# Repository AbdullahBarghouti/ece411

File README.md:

# ECE411

Practicum project for ECE 411

# Credits

Travis Hermant

Josh Davis

Abdullah Barghouti

Ammar Khan

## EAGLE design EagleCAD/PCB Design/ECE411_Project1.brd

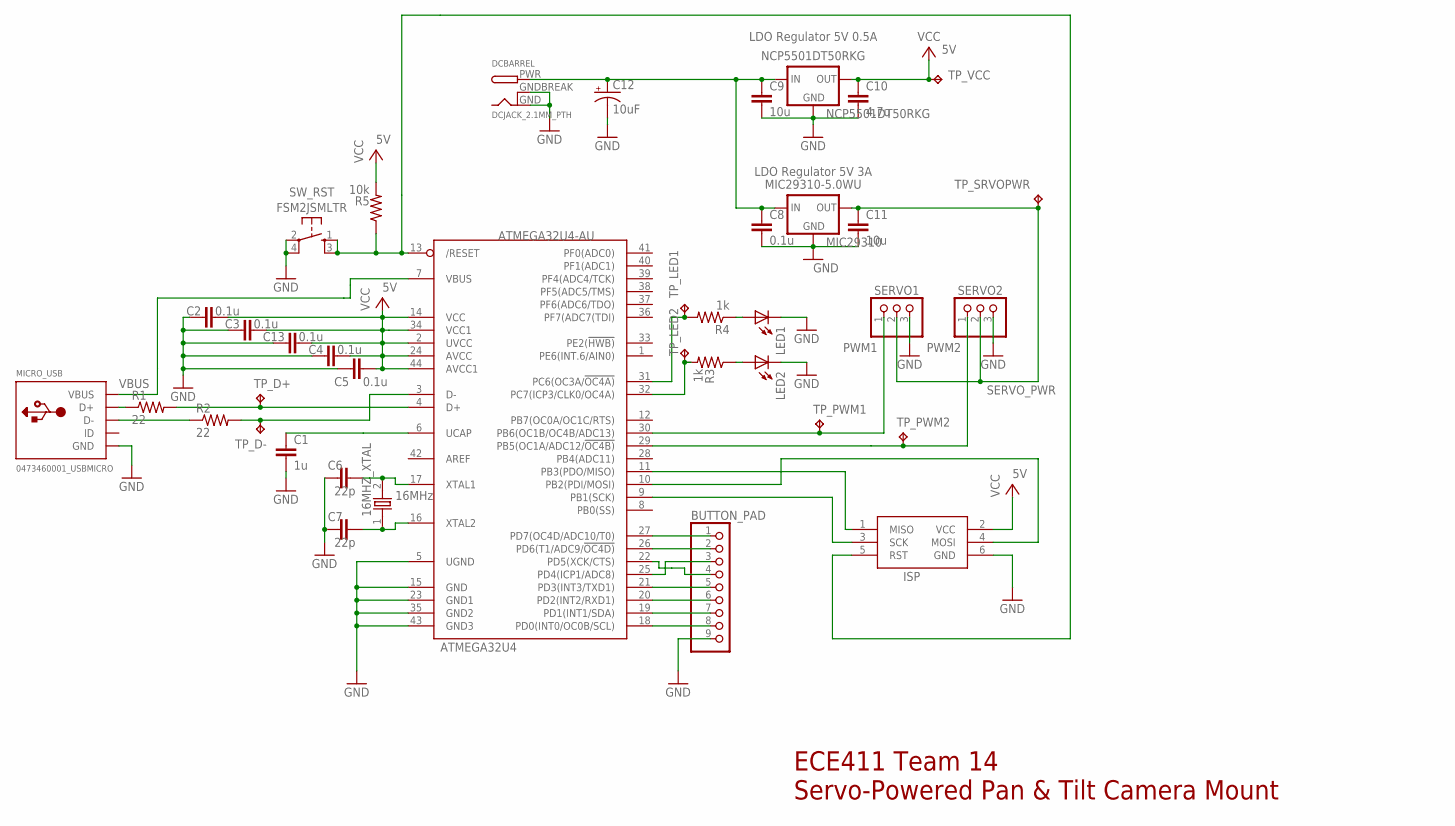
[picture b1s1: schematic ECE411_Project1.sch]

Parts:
16MHZ_XTAL: 16MHz; ATS160SM-1
ATMEGA32U4: ATMEGA32U4-AU; TQFP44
BUTTON_PAD: PINHD-1X9; 1X09
C1: 1u; C1206
C2, C3, C4, C5, C8, C13: 0.1u; C1206
C6, C7: 22p; C0805
C9, C11: 10u; C1206
C10: 4.7u; C1206
C12: 10uF; UD-5X5,4_NICHICON
DCBARREL: DCJACK_2.1MM_PTH
ISP: AVRISP-6; AVRISP
LED1, LED2: LEDSMT1206; 1206
MIC29310: MIC29310-5.0WU; TO-263/D2PAK
MICRO_USB: 0473460001_USBMICRO; MOLEX_USBMICRO
NCP5501DT50RKG: NCP5501DT50RKG; TO-263/D2PAK
R1, R2: 22; R1206
R3, R4: 1k; R1206
R5: 10k; R1206
SERVO1, SERVO2: PINHD-1X3; 1X03
SW_RST: FSM2JSMLTR
TP_D+: TPTP20SQ; TP20SQ
TP_D-: TPTP20SQ; TP20SQ
TP_LED1, TP_LED2: TPTP20SQ; TP20SQ
TP_PWM1, TP_PWM2: TPTP20SQ; TP20SQ
TP_SRVOPWR: TPTP20SQ; TP20SQ
TP_VCC: TPTP20SQ; TP20SQ

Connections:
/RST: ATMEGA32U4.13 (/RESET), ISP.5 (RST), R5.1, SW_RST.1, SW_RST.3
CHIP_LED1: ATMEGA32U4.31 (PC6(OC3A/!OC4A)), R4.2, TP_LED1.TP
CHIP_LED2: ATMEGA32U4.32 (PC7(ICP3/CLK0/OC4A)), R3.2, TP_LED2.TP
D+MCU: ATMEGA32U4.4 (D+), R1.2, TP_D+.TP
D+USB: MICRO_USB.3 (D+), R1.1
D-MCU: ATMEGA32U4.3 (D-), R2.2, TP_D-.TP
D-USB: MICRO_USB.2 (D-), R2.1
GND: ATMEGA32U4.5 (UGND), ATMEGA32U4.15 (GND), ATMEGA32U4.23 (GND1), ATMEGA32U4.35 (GND2), ATMEGA32U4.43 (GND3), BUTTON_PAD.9, C1.2, C2.1, C3.1, C4.1, C5.1, C6.1, C7.1, C8.2, C9.2, C10.2, C11.2, C12.-, C13.1, DCBARREL.GND, DCBARREL.GNDBREAK, ISP.6 (GND), LED1.C, LED2.C, MIC29310.2 (GND), MICRO_USB.5 (GND), MICRO_USB.G1 (GND), MICRO_USB.G2 (GND), MICRO_USB.G3 (GND), MICRO_USB.G4 (GND), MICRO_USB.G5 (GND), MICRO_USB.G6 (GND), NCP5501DT50RKG.2 (GND), SERVO1.3, SERVO2.3, SW_RST.2, SW_RST.4
unnamed: ATMEGA32U4.27 (PD7(OC4D/ADC10/T0)), BUTTON_PAD.1
unnamed: ATMEGA32U4.26 (PD6(T1/ADC9/!OC4D)), BUTTON_PAD.2
unnamed: ATMEGA32U4.25 (PD4(ICP1/ADC8)), BUTTON_PAD.3
unnamed: ATMEGA32U4.22 (PD5(XCK/CTS)), BUTTON_PAD.4
unnamed: ATMEGA32U4.21 (PD3(INT3/TXD1)), BUTTON_PAD.5
unnamed: ATMEGA32U4.20 (PD2(INT2/RXD1)), BUTTON_PAD.6
unnamed: LED2.A, R3.1
unnamed: LED1.A, R4.1
unnamed: ATMEGA32U4.19 (PD1(INT1/SDA)), BUTTON_PAD.7
unnamed: ATMEGA32U4.18 (PD0(INT0/OC0B/SCL)), BUTTON_PAD.8
unnamed: ATMEGA32U4.11 (PB3(PDO/MISO)), ISP.1 (MISO)
unnamed: ATMEGA32U4.10 (PB2(PDI/MOSI)), ISP.4 (MOSI)
unnamed: ATMEGA32U4.9 (PB1(SCK)), ISP.3 (SCK)
PWM1: ATMEGA32U4.30 (PB6(OC1B/OC4B/ADC13)), SERVO1.1, TP_PWM1.TP
PWM2: ATMEGA32U4.29 (PB5(OC1A/ADC12/!OC4B)), SERVO2.1, TP_PWM2.TP
SERVO_PWR: C11.1, MIC29310.3 (OUT), SERVO1.2, SERVO2.2, TP_SRVOPWR.TP
UCAP: ATMEGA32U4.6 (UCAP), C1.1
UNREG_PWR: C8.1, C9.1, C12.+, DCBARREL.PWR, MIC29310.1 (IN), NCP5501DT50RKG.1 (IN)
VBUS: ATMEGA32U4.7 (VBUS), MICRO_USB.1 (VBUS)
VCC: ATMEGA32U4.2 (UVCC), ATMEGA32U4.14 (VCC), ATMEGA32U4.24 (AVCC), ATMEGA32U4.34 (VCC1), ATMEGA32U4.44 (AVCC1), C2.2, C3.2, C4.2, C5.2, C10.1, C13.2, ISP.2 (VCC), NCP5501DT50RKG.3 (OUT), R5.2, TP_VCC.TP
XTAL1: 16MHZ_XTAL.2, ATMEGA32U4.17 (XTAL1), C6.2
XTAL2: 16MHZ_XTAL.1, ATMEGA32U4.16 (XTAL2), C7.2

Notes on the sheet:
LDO Regulator 5V 0.5A
LDO Regulator 5V 3A
ECE411 Team 14 Servo-Powered Pan & Tilt Camera Mount

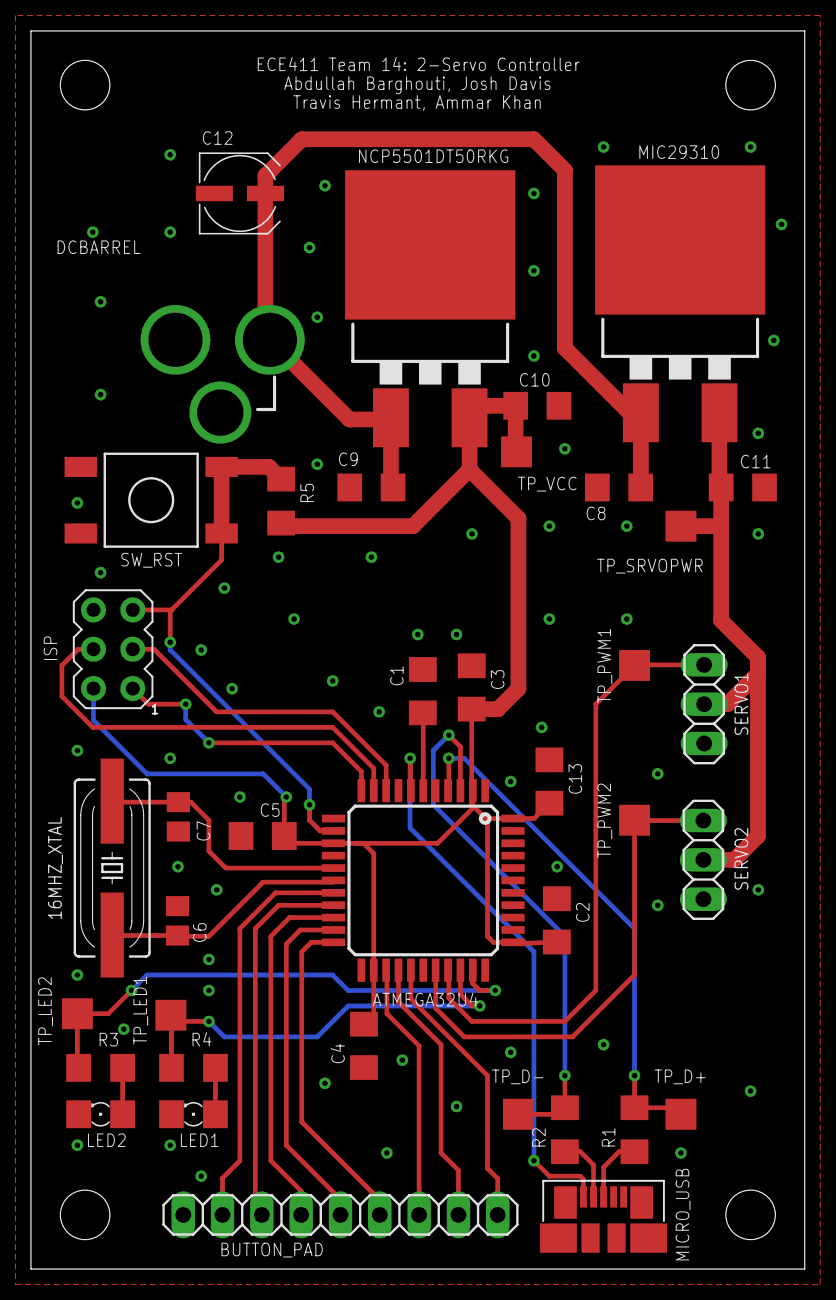
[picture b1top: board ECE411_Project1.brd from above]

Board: 2 copper layers, 50.0 x 80.0 mm, 39 parts (0 on the bottom side), 30 nets.

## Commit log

2018-10-10 Added Project Proposal document and a text document containing helpful git commands for the command prompt
2018-10-24 Added Itsy Bitsy EagleCad schematic to the repo
2018-10-24 Added Indroducting Itsy Bitsy 32u4 document
2018-10-24 added Sparkfun and Adafruit libraries to the EagleCad folder
2018-10-25 Add files via upload
    Preliminary schematic
2018-10-25 Create Preliminary schematic
2018-10-25 Added push button for ~Reset pin; named USB port
2018-10-25 removed empty schematic1 EagleCAD file
2018-10-25 Beautified the circuit: rotated and connected the servos directly to the ATMega32U4
2018-10-26 Added ISP 6-pin port to the schematic
2018-10-26 Added first version of Consolidated Links word document just for the sake of it.
2018-10-29 added the Product Design Specification (PDS) document to the repository
2018-10-29 Updated the price in the PDS to $45
2018-10-29 renamed docs folder to documents
2018-11-01 Added EagleCad workshop notes, updated Links word doc
2018-11-01 In-Progress schematic: working to add voltage regulators
2018-11-02 Cleaning up
2018-11-03 Added Custom libraries - one for the NE5532 example from the workshop and one for the L7805ABV voltage regulator from the EPL.
2018-11-03 Updated Links document
2018-11-03 Made Xtal library file
2018-11-03 updates to schematic
2018-11-03 Updating schematic... Updated Links document.
2018-11-04 Added some custom library components, updated schematic with new xtal cap values, and updated links document
2018-11-04 Updating schematic,added push button library file
2018-11-04 updates to library files
2018-11-04 Updated Schematic
2018-11-04 Visually complete schematic - nets need to be named still, and erc needs to be run.
2018-11-04 changed xtal caps to 0805 size from 1206
2018-11-04 Updated schematic with new DC barrel component that is thru-hole 2.1MM size
2018-11-04 Started the PCB - Everything's on the board and messy!
2018-11-04 Added test points all over the place
2018-11-05 Add files via upload
    connections made and test passed
2018-11-06 Updated schem and brd files
2018-11-06 Fixed a couple ERC errors... there are a couple left still.
2018-11-07 added electrolytic cap to schematic
2018-11-07 added electrolytic cap custom library
2018-11-08 added design review for Team 7
2018-11-08 Added in-progress design review notes from Team 7 for our project
2018-11-08 Restarted the PCB layout process, and created new schematic and layout files to use. The new file names removed the _RE at the end, they're titled ECE411_Project1
2018-11-08 updated in-progress PCB layout
2018-11-08 in-progress updates: Connected Vbuses in schematic, organized the new layout design
2018-11-08 In-progress updates: Connected UVCC to power and added a capacitor for it
2018-11-08 In-Progress Updates: Still fitting out the layout board file
2018-11-09 In progress - almost finished layout
2018-11-09 Add files via upload
    Here is the completed Bill of Materials.
2018-11-09 Updated the Bill of Materials
    Added the material numbers along with the package number
2018-11-09 Bill of Materials Updated
    This BOM has the package numbers along with the device numbers
2018-11-09 rearranged old eagle files into subfolder
2018-11-09 This is the old one
2018-11-09 This is also the old one
2018-11-09 clean
2018-11-09 Adding BOM
2018-11-09 updated BOM, completed Layout. Still need to add team number and project description to schematic
2018-11-09 added name and project description to schematic
2018-11-09 Added team number and project device description, and fixed what layer it goes in.
2018-11-09 Revising the review from group 7
2018-11-10 Updated the Board Layout: Added stitching vias, double gnd planes, set isolate distance to 10mils, smashed all the components and made their tnames look cohesive.
2018-11-10 updated the links backup document in this repository
2018-11-12 Updated board layout: moved power trace over so it wouldn't potentially bridge with the adjacent 32U4 pin; also moved button pad headers away from USB
2018-11-13 updated the BOM excel
2018-11-13 Updated BOM
2018-11-14 Changed the schematic: moved the LEDs, and outputted the whole D port to a 9-pin header, with the ninth pin going to ground for the button pad.
2018-11-14 Updated the schematic and the layout to output port D.
2018-11-14 Added Arrow BOM excel file, and updated our BOM excel file to include the two headers we'll order
2018-11-15 Added 3.2mm drill holes to the four corners of the layout
2018-11-16 Fixed pins for arduino configuration
2018-11-16 Some bootloader notes
2018-11-16 with avrdude instructions
2018-11-16 Updated Arrow BOM which has been ordered.
2018-11-29 Block diagrams
2018-11-29 Added hw for week 9
2018-11-29 Revert "Merge branch 'master' of https://github.com/travishermant/ece411"
    This reverts commit 2aba3d293e08243a46114a5186f8fb434fec35c3, reversing
    changes made to 6043273a4b8acb58a6e37cfb1f4f764bcff54ea6.
2018-12-02 Travis's preliminary updates to the Arduino Code.
2018-12-04 Travis's next gen code resolving the issue of getting stuck on full rotation. Still need to resolve the collision issue between servos.
2018-12-05 Setting boundaries
